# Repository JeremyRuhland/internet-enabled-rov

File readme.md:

Internet Enabled ROV
====================

Theory
------

The ROV will be connected to the surface by cat5 ethernet cable, carrying data and PoE at 12-48 volts depending on what power supply I find.

The underwater component will contain a motherboard, power converter and ip camera.

The motherboard contains a passive ethernet hub, connections to the power converter, microcontroller and motor drivers. The system can be programmed by usb connection.

When the motorboard's ip address is visited in a web browser, it responds with a simple html page showing instructions and a live updating camera feed. Pressing the WASD, QE and up/down arrow keys will send GET requests to the onboard webserver that will control the motor drivers. There is also a checkbox that will control an led array for increased lighting.

ROV Design
----------

The ROV will have four motors, one each for movement in the X, Y and Z axises and one for rotation of the robot.

All electronics will be encased in a waterproofed pvc pipe that will form the body of the ROV with a window endcap on one side and 5 waterproofed electrical connections on the other. Bits of foam will be used to achieve neutral density.

Motors will be standard brushed dc, placed inside pill bottles filled with paraffin and marine jelly for waterproofing. Propellers will be whatever I can get my hands on.

Embedded Webserver
------------------

Code for the embedded server is based off examples from jcw's [ethercard project](https://github.com/jcw/ethercard).

The javascript keyboard interface was inspired by a number of online tutorials and compressed to minimal size using google's [Closure Compiler](http://closure-compiler.appspot.com/).

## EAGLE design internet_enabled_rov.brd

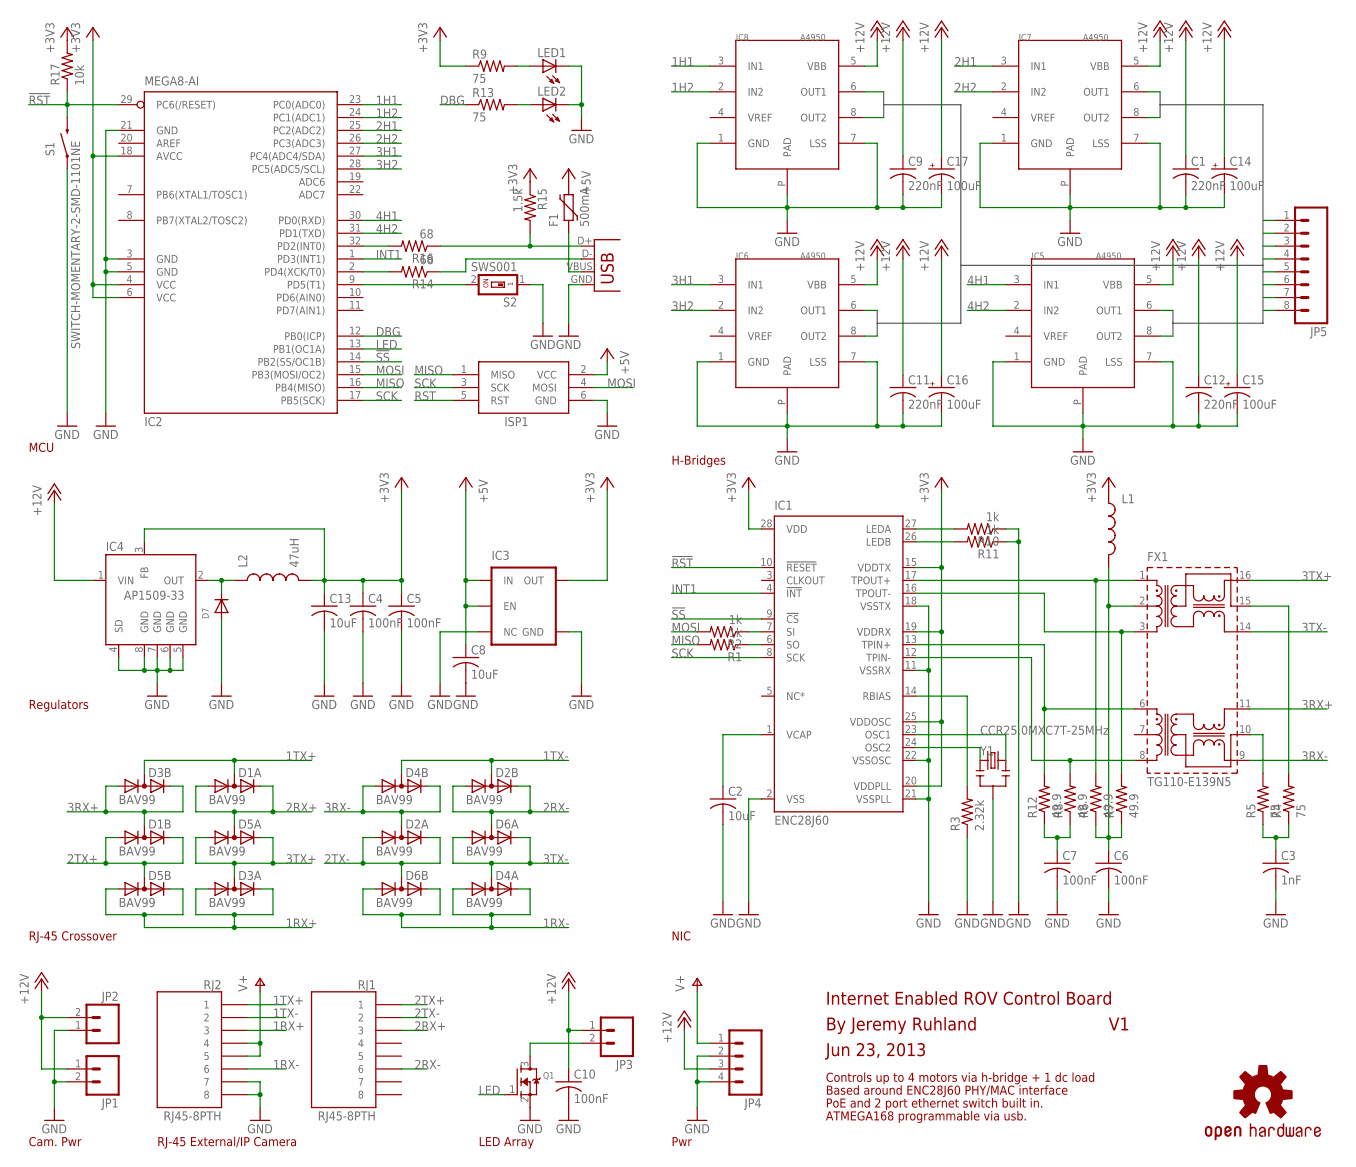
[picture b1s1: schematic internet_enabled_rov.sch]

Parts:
C1, C9, C11, C12: 220nF; C1206
C2, C8, C13: 10uF; C1206
C3: 1nF; C1206
C4, C5, C6, C7, C10: 100nF; C1206
C14, C15, C16, C17: 100uF; PANASONIC_D
D1, D2, D3, D4, D5, D6: BAV99; SOT363
D7: DIODESOD-123; SOD-123
F1: 500mA; PTC0805
FX1: TG110-E139N5; N5
IC1: ENC28J60; SO28W
IC2: MEGA8-AI; TQFP32-08
IC3: V_REG_TPS76433SOT23-5; SOT23-5
IC4: AP1509-33; SOP-8
IC5, IC6, IC7, IC8: A4950; SOIC-8-PAD
ISP1: AVRISP-6; AVRISP
JP1, JP2, JP3: M02LOCK; 1X02_LOCK
JP4: M04SCREW_LOCK; SCREWTERMINAL-3.5MM-4_LOCK
JP5: M083.5MM-8; SCREWTERMINAL-3.5MM-8
L1: INDUCTOR1210; 1210
L2: 47uH; 1210
LED1, LED2: LEDCHIPLED_1206; CHIPLED_1206
Q1: MOSFET-NREFLOW; SOT23
R1, R2, R10, R11: 1k; R1206
R3: 2.32k; R1206
R4, R5, R9, R13: 75; R1206
R6, R7, R8, R12: 49.9; R1206
R14, R16: 68; R1206
R15: 1.5k; R1206
R17: 10k; R1206
RJ1, RJ2: RJ45-8PTH; RJ45-8
S1: SWITCH-MOMENTARY-2-SMD-1101NE; TACTILE-SWITCH-1101NE
S2: SWS001; SMS-001
U$1: OSHW-LOGOL; OSHW-LOGO-L
X1: USBSMD; USB-MINIB
Y1: CCR25.0MXC7T-25MHz; RESONATOR-SMD

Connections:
1H1: IC2.23 (PC0(ADC0)), IC8.3 (IN1)
1H2: IC2.24 (PC1(ADC1)), IC8.2 (IN2)
1RX+: D3.1 (A), D3.2 (K), D5.4 (A), D5.5 (K), RJ2.3
1RX-: D4.1 (A), D4.2 (K), D6.4 (A), D6.5 (K), RJ2.6
1TX+: D1.6 (AK), D3.3 (AK), RJ2.1
1TX-: D2.3 (AK), D4.3 (AK), RJ2.2
2H1: IC2.25 (PC2(ADC2)), IC7.3 (IN1)
2H2: IC2.26 (PC3(ADC3)), IC7.2 (IN2)
2RX+: D1.1 (A), D1.2 (K), D5.6 (AK), RJ1.3
2RX-: D2.4 (A), D2.5 (K), D6.6 (AK), RJ1.6
2TX+: D1.4 (A), D1.5 (K), D5.3 (AK), RJ1.1
2TX-: D2.1 (A), D2.2 (K), D6.3 (AK), RJ1.2
3H1: IC2.27 (PC4(ADC4/SDA)), IC6.3 (IN1)
3H2: IC2.28 (PC5(ADC5/SCL)), IC6.2 (IN2)
3RX+: D1.3 (AK), D3.4 (A), D3.5 (K), FX1.11
3RX-: D2.6 (AK), D4.4 (A), D4.5 (K), FX1.9
3TX+: D3.6 (AK), D5.1 (A), D5.2 (K), FX1.16
3TX-: D4.6 (AK), D6.1 (A), D6.2 (K), FX1.14
4H1: IC2.30 (PD0(RXD)), IC5.3 (IN1)
4H2: IC2.31 (PD1(TXD)), IC5.2 (IN2)
!RST: IC1.10 (!RESET), IC2.29 (PC6(/RESET)), R17.1, S1.P$2 (2)
!SS: IC1.9 (!CS), IC2.14 (PB2(SS/OC1B))
+3V3: C4.1, C5.1, C13.1, IC1.15 (VDDTX), IC1.19 (VDDRX), IC1.20 (VDDPLL), IC1.25 (VDDOSC), IC1.28 (VDD), IC2.4 (VCC), IC2.6 (VCC), IC2.18 (AVCC), IC3.5 (OUT), IC4.3 (FB), L1.1, L2.2, R9.1, R15.1, R17.2
+5V: C8.1, F1.2, IC3.1 (IN), IC3.3 (EN), ISP1.2 (VCC)
+12V: C1.1, C9.1, C10.1, C11.1, C12.1, C14.+, C15.+, C16.+, C17.+, IC4.1 (VIN), IC5.5 (VBB), IC6.5 (VBB), IC7.5 (VBB), IC8.5 (VBB), JP1.1, JP2.2, JP3.1, JP4.3
DBG: IC2.12 (PB0(ICP)), R13.1
GND: C1.2, C2.2, C3.2, C4.2, C5.2, C6.2, C7.2, C8.2, C9.2, C10.2, C11.2, C12.2, C13.2, C14.-, C15.-, C16.-, C17.-, D7.A, IC1.2 (VSS), IC1.11 (VSSRX), IC1.18 (VSSTX), IC1.21 (VSSPLL), IC1.22 (VSSOSC), IC2.3 (GND), IC2.5 (GND), IC2.21 (GND), IC3.2 (GND), IC3.4 (NC), IC4.4 (SD), IC4.5 (GND), IC4.6 (GND), IC4.7 (GND), IC4.8 (GND), IC5.1 (GND), IC5.7 (LSS), IC5.P (PAD), IC6.1 (GND), IC6.7 (LSS), IC6.P (PAD), IC7.1 (GND), IC7.7 (LSS), IC7.P (PAD), IC8.1 (GND), IC8.7 (LSS), IC8.P (PAD), ISP1.6 (GND), JP1.2, JP2.1, JP4.2, JP4.4, LED1.C, LED2.C, Q1.2 (S), R3.1, R10.1, R11.1, RJ2.7, RJ2.8, S1.P$1 (1), S2.1, X1.GND, Y1.2
INT1: IC1.4 (!INT), IC2.1 (PD3(INT1))
LED: IC2.13 (PB1(OC1A)), Q1.1 (G)
MISO: IC2.16 (PB4(MISO)), ISP1.1 (MISO), R1.2
MOSI: IC2.15 (PB3(MOSI/OC2)), ISP1.4 (MOSI), R2.2
unnamed: IC1.6 (SO), R1.1
unnamed: F1.1, X1.VBUS
unnamed: LED1.A, R9.2
unnamed: LED2.A, R13.2
unnamed: IC1.7 (SI), R2.1
unnamed: D7.C, IC4.2 (OUT), L2.1
unnamed: FX1.10, R5.2
unnamed: FX1.15, R4.2
unnamed: IC2.32 (PD2(INT0)), R16.2
unnamed: IC2.2 (PD4(XCK/T0)), R14.2
unnamed: IC2.9 (PD5(T1)), S2.2
unnamed: JP3.2, Q1.3 (D)
unnamed: C3.1, R4.1, R5.1
unnamed: C7.1, R8.1, R12.1
unnamed: C6.1, FX1.2, L1.2, R6.1, R7.1
unnamed: FX1.3, IC1.16 (TPOUT-), R7.2
unnamed: FX1.1, IC1.17 (TPOUT+), R6.2
unnamed: FX1.8, IC1.12 (TPIN-), R8.2
unnamed: FX1.6, IC1.13 (TPIN+), R12.2
unnamed: R15.2, R16.1, X1.D+
unnamed: R14.1, X1.D-
unnamed: C2.1, IC1.1 (VCAP)
unnamed: IC1.14 (RBIAS), R3.2
unnamed: IC1.24 (OSC2), Y1.1
unnamed: IC1.23 (OSC1), Y1.3
unnamed: IC1.27 (LEDA), R10.2
unnamed: IC1.26 (LEDB), R11.2
OUT1: IC8.8 (OUT2), JP5.2
OUT2: IC8.6 (OUT1), JP5.1
OUT3: IC7.8 (OUT2), JP5.4
OUT4: IC7.6 (OUT1), JP5.3
OUT5: IC6.8 (OUT2), JP5.6
OUT6: IC6.6 (OUT1), JP5.5
OUT7: IC5.8 (OUT2), JP5.8
OUT8: IC5.6 (OUT1), JP5.7
RST: ISP1.5 (RST)
SCK: IC1.8 (SCK), IC2.17 (PB5(SCK)), ISP1.3 (SCK)
V+: JP4.1, RJ2.4, RJ2.5

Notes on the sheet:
RJ-45 External/IP Camera
LED Array
Pwr
Regulators
MCU
NIC
H-Bridges
RJ-45 Crossover
Cam. Pwr
Internet Enabled ROV Control Board
By Jeremy Ruhland
Based around ENC28J60 PHY/MAC interface
Controls up to 4 motors via h-bridge + 1 dc load
Jun 23, 2013
PoE and 2 port ethernet switch built in.
ATMEGA168 programmable via usb.

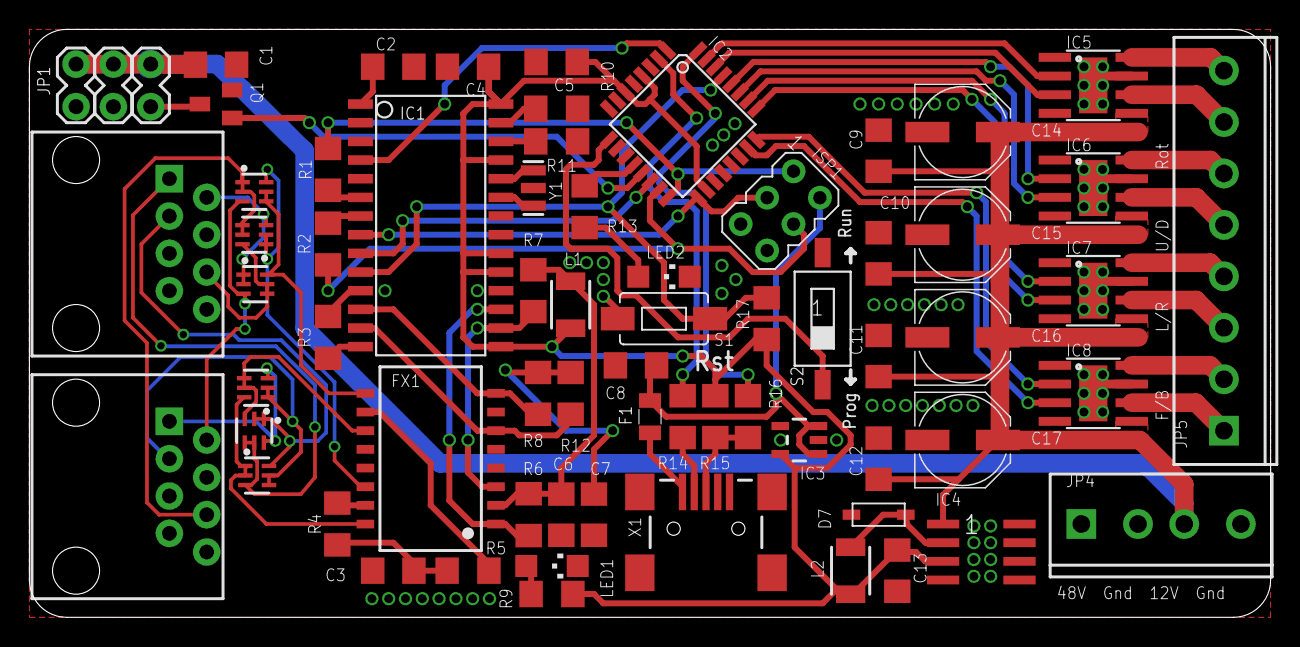
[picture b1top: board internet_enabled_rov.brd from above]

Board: 2 copper layers, 84.5 x 40.0 mm, 69 parts (1 on the bottom side), 68 nets.

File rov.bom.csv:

Qty	Digikey Part Number	Value	Device	Parts
4	1276-1106-1-ND	220nF	C-USC1206	C1,C9,C11,C12
4	PCE4238CT-ND	100uF	CAP_POLD	C14,C15,C16,C17
3	399-8013-1-ND	10uF	C-USC1206	C2,C8,C13
1	1276-1772-1-ND	1nF	C-USC1206	C3
5	1276-1007-1-ND	100nF	C-USC1206	C4,C5,C6,C7,C10
6	568-8205-1-ND		BAV99	D1,D2,D3,D4,D5,D6
1	MBR130LSFT1GOSCT-ND		DIODESOD-123	D7
1	507-1517-1-ND	500mA	FUSE_PTC-0805	F1
1	507-1468-1-ND		TG110-E139N5	FX1
1	ENC28J60-I/SO-ND		ENC28J60	IC1
1	ATMEGA168A-AU-ND	MCU	MEGA8-AI	IC2
1	MCP1824T-3302E/OTCT-ND	3.3V	V_REG_SOT23-5	IC3
1	AP1509-33SGDICT-ND	3.3V	AP1509	IC4
4	620-1400-1-ND		A4950	IC5,IC6,IC7,IC8
1	ED2742-ND	3.5MM	M04SCREW_LOCK	JP4
1	A98041-ND	3.5MM	M08SCREW_LOCK	JP5
1	CM322522-100KLCT-ND	FERRITE BEAD	INDUCTOR1210	L1
1	587-1627-1-ND	47uH	INDUCTOR1210	L2
2	475-1416-1-ND	RED	LEDCHIPLED_1206	LED1,LED2
1	IRLML6344TRPBFCT-ND	N-CH 30V 5A FET	MOSFET-NREFLOW	Q1
4	RMCF1206FT1K00CT-ND	1k	R-US_R1206	R1,R2,R10,R11
2	RMCF1206FT68R0CT-ND	68	R-US_R1206	R14,R16
1	RMCF1206FT1K50CT-ND	1.5k	R-US_R1206	R15
1	RMCF1206FT10K0CT-ND	10k	R-US_R1206	R17
1	RMCF1206FT2K32CT-ND	2.3k	R-US_R1206	R3
4	RMCF1206FT75R0CT-ND	75	R-US_R1206	R4,R5,R9,R13
4	RMCF1206FT49R9CT-ND	49.9	R-US_R1206	R6,R7,R8,R12
2	609-1046-ND		RJ45-8PTH	RJ1,RJ2
1	450-1140-ND	2-SMD-1101NE	SWITCH-MOMENTARY	S1
1	563-1004-1-ND	SWS001	SWITCH-DIP	S2
1	ED2992CT-ND		USBSMD	X1
1	445-1650-1-ND	25MHz	RESONATORSMD	Y1

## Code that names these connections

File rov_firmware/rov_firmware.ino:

// UDP firmware for internet enabled ROV
// By Jeremy Ruhland
// Based off example code by Brian Lee <cybexsoft@hotmail.com>

#define stopAllMotors() PORTC &= ~((1<<PC5)|(1<<PC4)|(1<<PC3)|(1<<PC2)|(1<<PC1)|(1<<PC0)); PORTD &= ~((1<<PD1)|(1<<PD0))
#define lightsOff() PORTB &= ~(1<<PB0)
#define lightsOn() PORTB |= (1<<PB0)
#define forwardThrust() PORTC |= (1<<PC0)
#define reverseThrust() PORTC |= (1<<PC1)
#define forwardReverseStop() PORTC &= ~((1<<PC1)|(1<<PC0)) 
#define starboardThrust() PORTC |= (1<<PC2)
#define portThrust() PORTC |= (1<<PC3)
#define starboardPortStop() PORTC &= ~((1<<PC3)|(1<<PC2))
#define diveThrust() PORTC |= (1<<PC4)
#define surfaceThrust() PORTC |= (1<<PC5)
#define diveSurfaceStop() PORTC &= ~((1<<PC5)|(1<<PC4))
#define clockwiseThrust() PORTD |= (1<<PD0)
#define anticlockwiseThrust() PORTD |= (1<<PD1)
#define clockwiseAnticlockwiseStop() PORTD &= ~((1<<PD1)|(1<<PD0))

#include <EtherCard.h>
#include <avr/eeprom.h>

// ethernet interface ip address
static byte myip[] = { 192,168,1,200 };
// ethernet interface mac address - must be unique on your network
static byte mymac[] = { 0x74,0x69,0x69,0x2D,0x30,0x31 };

byte Ethernet::buffer[1200];   // tcp/ip send and receive buffer
static BufferFiller bfill; // used as cursor while filling the buffer

char functionName[2];	// query key of sent command

char okHeader[] PROGMEM = 
    "HTTP/1.0 200 OK\r\n"
    "Content-Type: text/html\r\n"
    "Pragma: no-cache\r\n"
;

char indexPage[] PROGMEM = 
    "<html><b>ROV Web Interface</b>"
    "<table><tr><td><iframe width=\"480\" height=\"302\" src=\"http://www.ustream.tv/embed/9948292\?v=3\"></iframe></td>"
    "<td><hr width=1 size=250></td><td>Keyboard controlls:<br>Arrow Keys and<br>A (Ascend)<br>Z (Descend)<br><br><label><input type=\'checkbox\' onchange=\'e(this);\'>Enable Lighting</label></td></tr></table>"
    "<script>var a;var b={};var i=document.createElement(\"img\");function c(e){if(a&&a.keyCode==e.keyCode)return;if(!e)e=window.event;a=e;b[e.keyCode]=true;if(e.keyCode==65)i.src=\"\?c=1\";if(e.keyCode==90)i.src=\"\?c=2\";if(e.keyCode==37)i.src=\"\?c=4\";if(e.keyCode==39)i.src=\"\?c=5\";if(e.keyCode==38)i.src=\"\?c=7\";if(e.keyCode==40)i.src=\"\?c=8\";if(e.keyCode==33)i.src=\"\?c=c\";if(e.keyCode==34)i.src=\"\?c=d\";}function d(e){a=null;delete b[e.keyCode];if(!e)e=window.event;if(e.keyCode==65||e.keyCode==90)i.src=\"\?c=3\";if(e.keyCode==37||e.keyCode==39)i.src=\"\?c=6\";if(e.keyCode==38||e.keyCode==40)i.src=\"\?c=9\";if(e.keyCode==33||e.keyCode==34)i.src=\"\?c=e\";}function e(cb){if(cb.checked==true)i.src=\"\?c=a\";else i.src=\"\?c=b\";}document.onkeydown=c;document.onkeyup=d;</script></html>"
;

static void homePage(BufferFiller& buf) {
    buf.emit_p(indexPage, okHeader);
}

static void commandParse(const char* data, BufferFiller& buf) {
    // execute command, if present
    switch(functionName[0]) {
	case '0':	// All motors off
                stopAllMotors();
		break;
	case '1':	// Up
	            surfaceThrust();
		break;
	case '2':	// Down
	            diveThrust();
		break;
	case '3':	// Up/down off
	            diveSurfaceStop();
		break;
	case '4':   // Left
	            portThrust();
		break;
	case '5':   // Right
	            starboardThrust();
		break;
	case '6':   // Left/right off
	            starboardPortStop();
		break;
	case '7':	// Fwd
	            forwardThrust();
		break;
	case '8':	// Back
	            reverseThrust();
		break;
	case '9':	// Fwd/back off
	            forwardReverseStop();
		break;
	case 'a':	// Lights on
	            lightsOn();
		break;
	case 'b':	// Lights off
	            lightsOff();
		break;
	case 'c':	// Rotate CW
	            clockwiseThrust();
		break;
	case 'd':	// Rotate CCW
	            anticlockwiseThrust();
		break;
    case 'e':   // Rotate off
                clockwiseAnticlockwiseStop();
        break;
	default:    // Emergency case, should never be entered
                stopAllMotors();
		break;
	}
}

void setup(){
    // Disable motors/lights
    PORTB &= ~(1<<PB1);
    PORTC &= ~((1<<PC5)|(1<<PC4)|(1<<PC3)|(1<<PC2)|(1<<PC1)|(1<<PC0));
    PORTD &= ~((1<<PD1)|(1<<PD0));
    // Set ouput ports correctly
    DDRB |= (1<<PB1);
    DDRC |= (1<<PC5)|(1<<PC4)|(1<<PC3)|(1<<PC2)|(1<<PC1)|(1<<PC0);
    DDRD |= (1<<PD1)|(1<<PD0);
    // Init ethernet system
    ether.begin(sizeof Ethernet::buffer, mymac);
    ether.staticSetup(myip);
}

void loop(){
    word len = ether.packetReceive();
    word pos = ether.packetLoop(len);
    // check if valid tcp data is received
    if (pos) {
        bfill = ether.tcpOffset();
        char* data = (char *) Ethernet::buffer + pos;
        // receive buf hasn't been clobbered by reply yet
        if (EtherCard::findKeyVal(data, functionName, 2, "c") != 0)
            commandParse(data, bfill);
        else
            homePage(bfill);
        ether.httpServerReply(bfill.position()); // send web page data
    }
}

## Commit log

2013-06-29 First commit, created repo
2013-06-29 Updated readme, fixed markdown issues.
2013-06-29 Added pcb images.

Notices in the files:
parts and their libraries:
sparkfun: Licensing: CC v3.0 Share-Alike You are welcome to use this library for commercial purposes.
